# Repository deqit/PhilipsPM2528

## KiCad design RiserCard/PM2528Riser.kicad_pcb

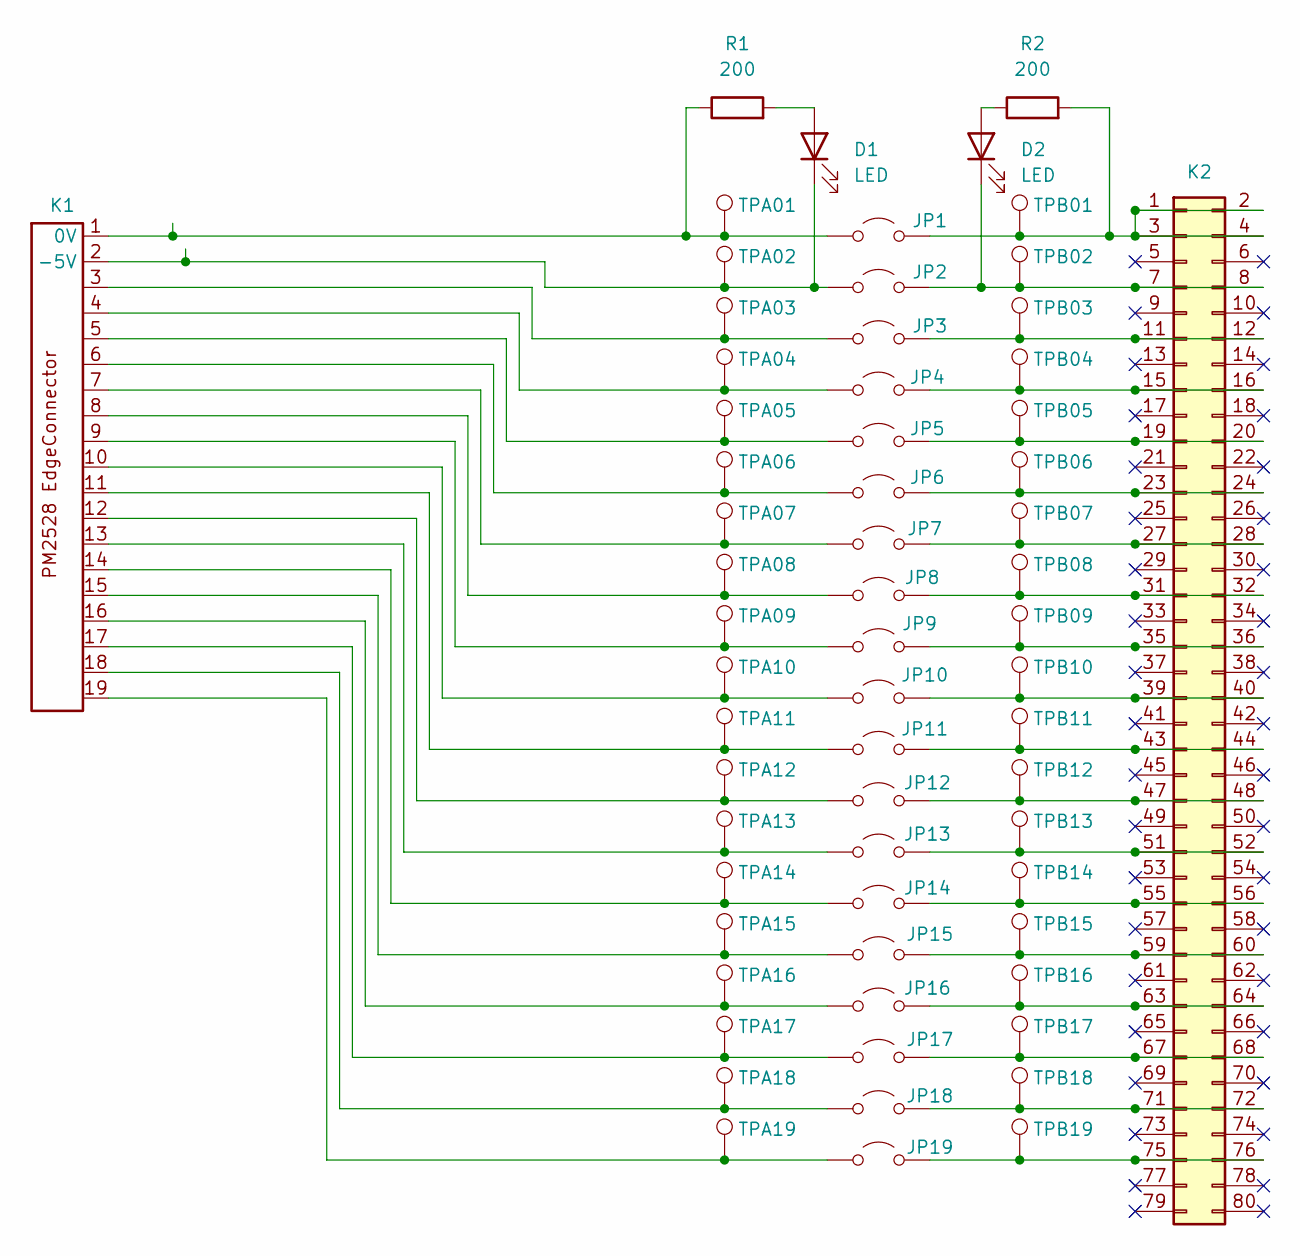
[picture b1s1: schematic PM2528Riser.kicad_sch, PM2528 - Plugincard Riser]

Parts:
D1, D2: LED; LED_0805_2012Metric
JP1, JP2, JP3, JP4, JP5, JP6, JP7, JP8, JP9, JP10, JP11, JP12, JP13, JP14, JP15, JP16, JP17, JP18, JP19: Jumper_2_Open; PinHeader_1x02_P2.54mm_Vertical
K1: PM2528_RiserCardConnector
K2: Conn_02x40_Odd_Even; CONN EDGE DUAL FMALE 80POS 0.100
R1, R2: 200; R_0805_2012Metric_Pad1.20x1.40mm_HandSolder
TPA01, TPA02, TPA03, TPA04, TPA05, TPA06, TPA07, TPA08, TPA09, TPA10, TPA11, TPA12, TPA13, TPA14, TPA15, TPA16, TPA17, TPA18, TPA19: TestPoint; Pin_D1.0mm_L10.0mm
TPB01, TPB02, TPB03, TPB04, TPB05, TPB06, TPB07, TPB08, TPB09, TPB10, TPB11, TPB12, TPB13, TPB14, TPB15, TPB16, TPB17, TPB18, TPB19: TestPoint; TestPoint_Loop_D1.80mm_Drill1.0mm_Beaded

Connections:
unnamed: D1.2 (A), R1.2
unnamed: D1.1 (K), JP2.1 (A), K1.2 (-5V), TPA02.1
unnamed: D2.2 (A), R2.1
unnamed: D2.1 (K), JP2.2 (B), K2.7, K2.8, TPB02.1
unnamed: JP1.1 (A), K1.1 (0V), R1.1, TPA01.1
unnamed: JP1.2 (B), K2.1, K2.2, K2.3, K2.4, R2.2, TPB01.1
unnamed: JP3.1 (A), K1.3, TPA03.1
unnamed: JP3.2 (B), K2.11, K2.12, TPB03.1
unnamed: JP4.1 (A), K1.4, TPA04.1
unnamed: JP4.2 (B), K2.15, K2.16, TPB04.1
unnamed: JP5.1 (A), K1.5, TPA05.1
unnamed: JP5.2 (B), K2.19, K2.20, TPB05.1
unnamed: JP6.1 (A), K1.6, TPA06.1
unnamed: JP6.2 (B), K2.23, K2.24, TPB06.1
unnamed: JP7.1 (A), K1.7, TPA07.1
unnamed: JP7.2 (B), K2.27, K2.28, TPB07.1
unnamed: JP8.1 (A), K1.8, TPA08.1
unnamed: JP8.2 (B), K2.31, K2.32, TPB08.1
unnamed: JP9.1 (A), K1.9, TPA09.1
unnamed: JP9.2 (B), K2.35, K2.36, TPB09.1
unnamed: JP10.1 (A), K1.10, TPA10.1
unnamed: JP10.2 (B), K2.39, K2.40, TPB10.1
unnamed: JP11.1 (A), K1.11, TPA11.1
unnamed: JP11.2 (B), K2.43, K2.44, TPB11.1
unnamed: JP12.1 (A), K1.12, TPA12.1
unnamed: JP12.2 (B), K2.47, K2.48, TPB12.1
unnamed: JP13.1 (A), K1.13, TPA13.1
unnamed: JP13.2 (B), K2.51, K2.52, TPB13.1
unnamed: JP14.1 (A), K1.14, TPA14.1
unnamed: JP14.2 (B), K2.55, K2.56, TPB14.1
unnamed: JP15.1 (A), K1.15, TPA15.1
unnamed: JP15.2 (B), K2.59, K2.60, TPB15.1
unnamed: JP16.1 (A), K1.16, TPA16.1
unnamed: JP16.2 (B), K2.63, K2.64, TPB16.1
unnamed: JP17.1 (A), K1.17, TPA17.1
unnamed: JP17.2 (B), K2.67, K2.68, TPB17.1
unnamed: JP18.1 (A), K1.18, TPA18.1
unnamed: JP18.2 (B), K2.71, K2.72, TPB18.1
unnamed: JP19.1 (A), K1.19, TPA19.1
unnamed: JP19.2 (B), K2.75, K2.76, TPB19.1

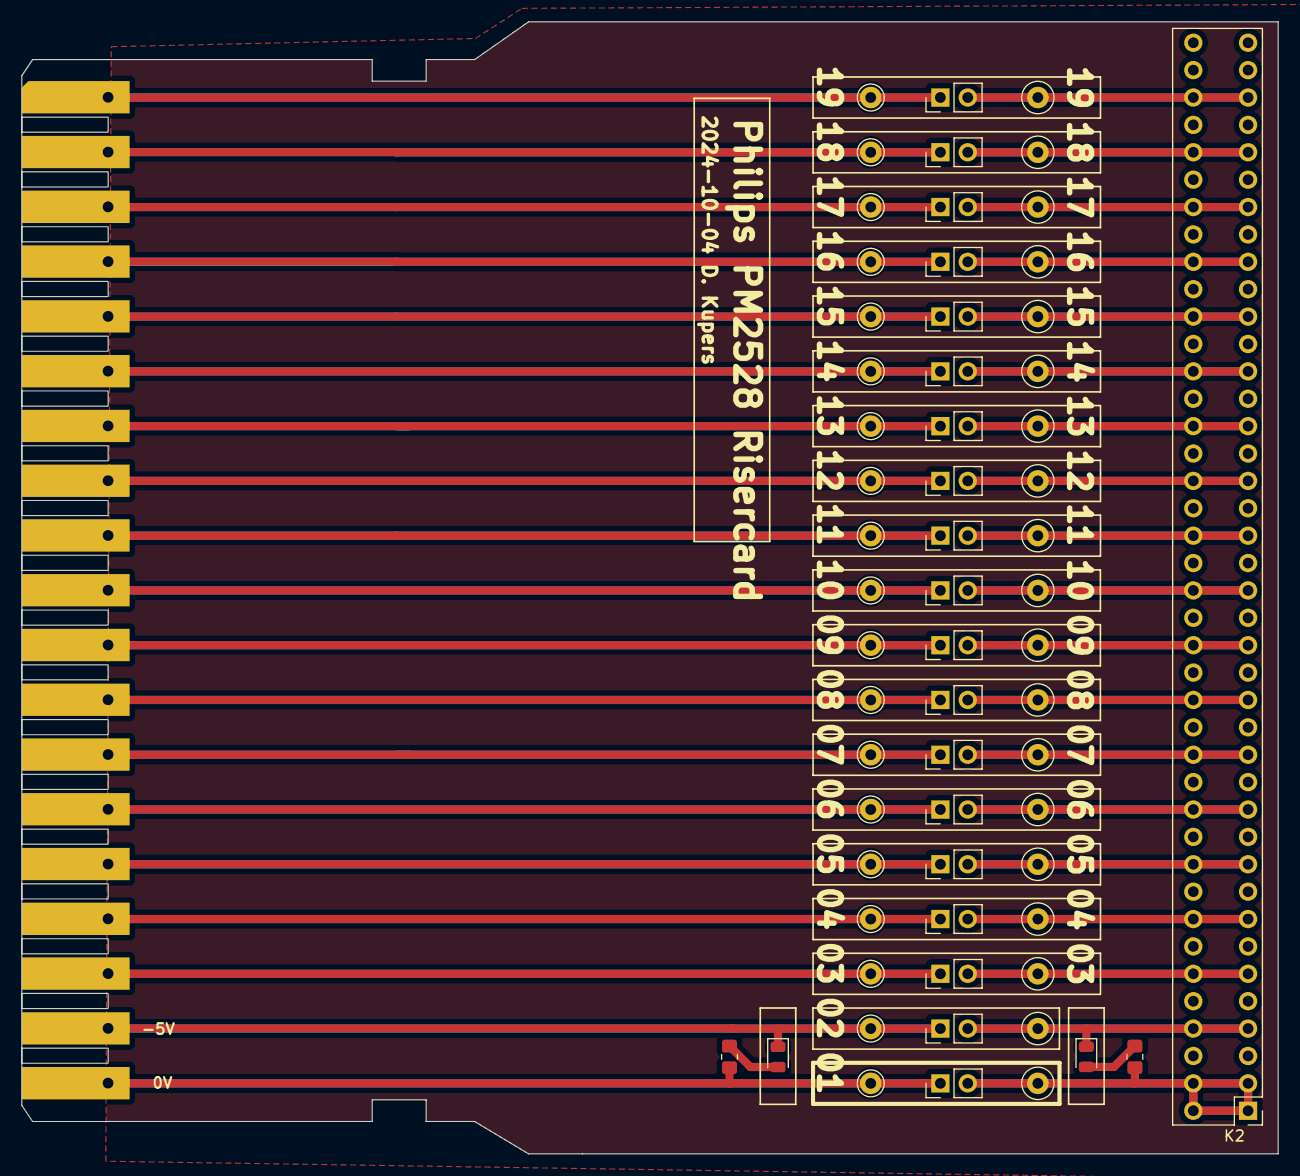
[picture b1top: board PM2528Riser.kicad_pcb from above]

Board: 2 copper layers, 116.5 x 105.0 mm, 63 parts (0 on the bottom side), 40 nets.

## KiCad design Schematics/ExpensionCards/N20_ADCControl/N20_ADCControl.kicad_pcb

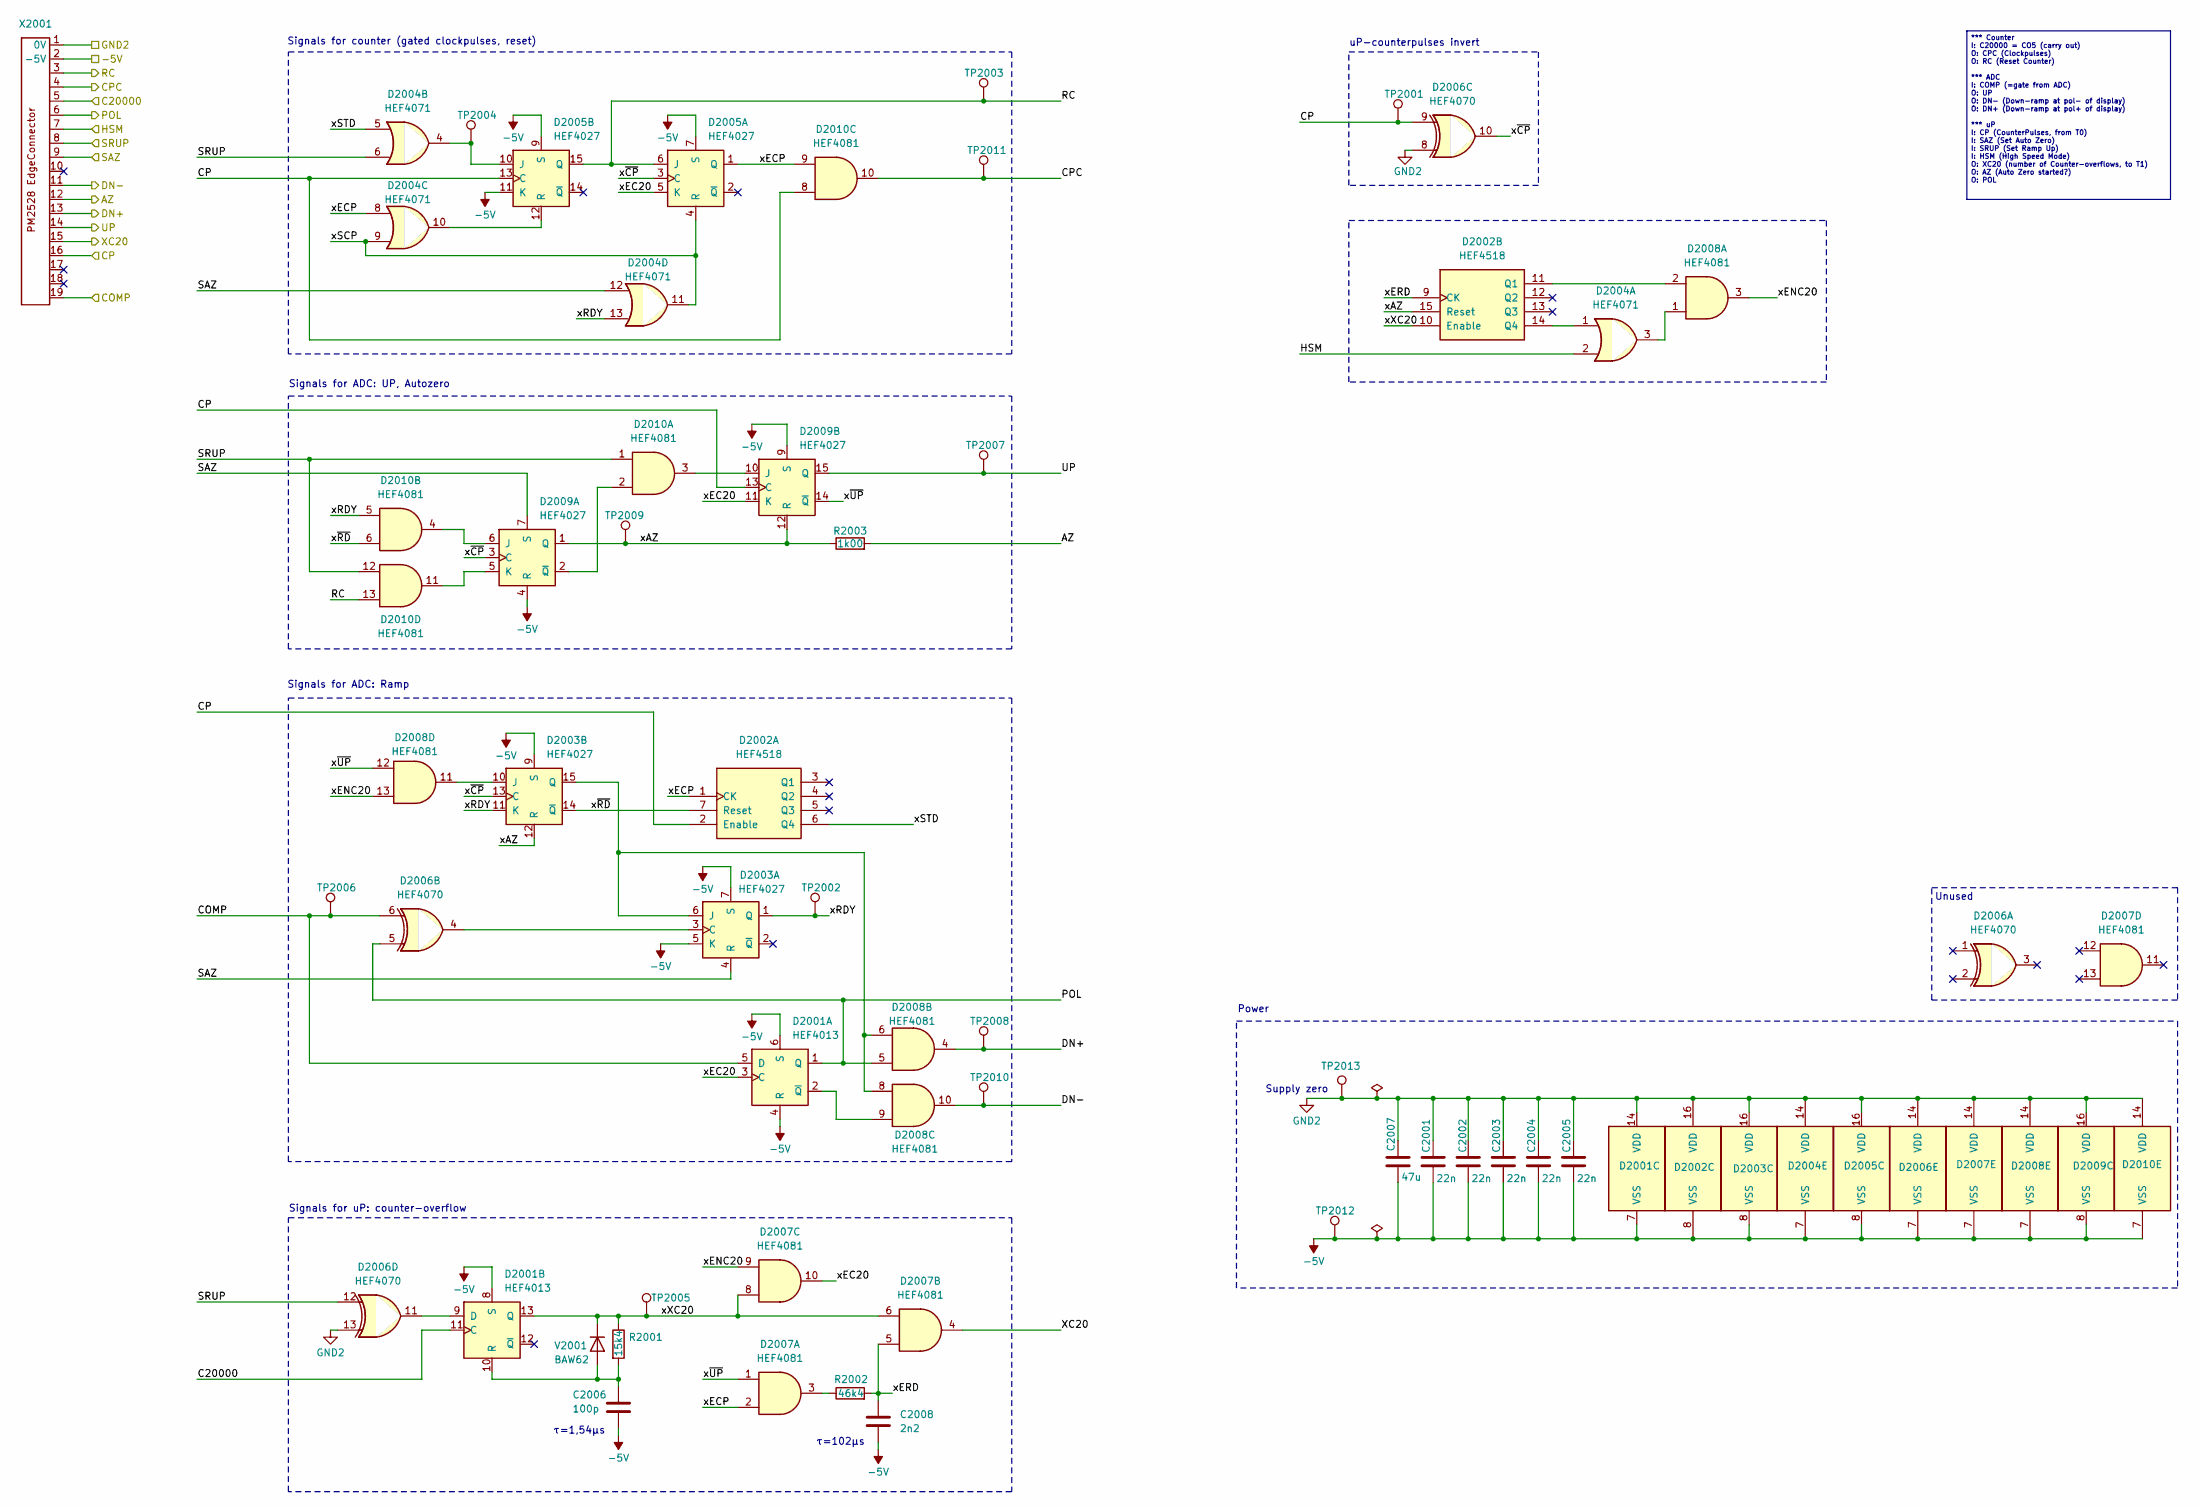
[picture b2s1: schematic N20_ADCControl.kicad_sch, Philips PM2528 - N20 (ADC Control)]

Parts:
C2001, C2002, C2003, C2004, C2005: 22n; C_Disc_D5.0mm_W2.5mm_P5.00mm
C2006: 100p; C_Disc_D5.0mm_W2.5mm_P5.00mm
C2007: 47u; CP_Axial_L10.0mm_D6.0mm_P15.00mm_Horizontal
C2008: 2n2; C_Disc_D5.0mm_W2.5mm_P5.00mm
D2001: HEF4013; DIP-14_W7.62mm
D2002: HEF4518; DIP-16_W7.62mm
D2003, D2005, D2009: HEF4027; DIP-16_W7.62mm
D2004: HEF4071; DIP-14_W7.62mm
D2006: HEF4070; DIP-14_W7.62mm
D2007, D2008, D2010: HEF4081; DIP-14_W7.62mm
R2001: 15k4; R_Axial_DIN0207_L6.3mm_D2.5mm_P10.16mm_Horizontal
R2002: 46k4; R_Axial_DIN0207_L6.3mm_D2.5mm_P10.16mm_Horizontal
R2003: 1k00; R_Axial_DIN0207_L6.3mm_D2.5mm_P10.16mm_Horizontal
TP2001, TP2002, TP2003, TP2004, TP2005, TP2006, TP2007, TP2008, TP2009, TP2010, TP2011, TP2012, TP2013: TestPoint; Pin_D0.9mm_L10.0mm_W2.4mm_FlatFork
V2001: BAW62; D_T-1_P10.16mm_Horizontal
X2001: PM2528_RiserCardConnector

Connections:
-5V: C2001.2, C2002.2, C2003.2, C2004.2, C2005.2, C2006.2, C2007.2, C2008.2, D2001.4 (R), D2001.6 (S), D2001.7 (VSS), D2001.8 (S), D2002.8 (VSS), D2003.5 (K), D2003.7 (S), D2003.8 (VSS), D2003.9 (S), D2004.7 (VSS), D2005.7 (S), D2005.8 (VSS), D2005.9 (S), D2005.11 (K), D2006.7 (VSS), D2007.7 (VSS), D2008.7 (VSS), D2009.4 (R), D2009.8 (VSS), D2009.9 (S), D2010.7 (VSS), TP2012.1, X2001.2 (-5V)
/AZ: R2003.2, X2001.12
/C20000: D2001.11 (C), X2001.5
/COMP: D2001.5 (D), D2006.6, TP2006.1, X2001.19
/CP: D2002.2 (Enable), D2005.13 (C), D2006.9, D2009.13 (C), D2010.8, TP2001.1, X2001.16
/CPC: D2010.10, TP2011.1, X2001.4
/DN+: D2008.4, TP2008.1, X2001.13
/DN-: D2008.10, TP2010.1, X2001.11
/HSM: D2004.2, X2001.7
/POL: D2001.1 (Q), D2006.5, D2008.5, X2001.6
/RC: D2005.6 (J), D2005.15 (Q), D2010.13, TP2003.1, X2001.3
/SAZ: D2003.4 (R), D2004.12, D2009.7 (S), X2001.9
/SRUP: D2004.6, D2006.12, D2010.1, D2010.12, X2001.8
/UP: D2009.15 (Q), TP2007.1, X2001.14
/XC20: D2007.4, X2001.15
/xAZ: D2002.15 (Reset), D2003.12 (R), D2009.1 (Q), D2009.12 (R), R2003.1, TP2009.1
/xEC20: D2001.3 (C), D2005.5 (K), D2007.10, D2009.11 (K)
/xECP: D2002.1 (CK), D2004.8, D2005.1 (Q), D2007.2, D2010.9
/xENC20: D2007.9, D2008.3, D2008.13
/xERD: C2008.1, D2002.9 (CK), D2007.5, R2002.2
/xRDY: D2003.1 (Q), D2003.11 (K), D2004.13, D2010.5, TP2002.1
/xSCP: D2004.9, D2004.11, D2005.4 (R)
/xSTD: D2002.6 (Q4), D2004.5
/xXC20: D2001.13 (Q), D2002.10 (Enable), D2007.6, D2007.8, R2001.1, TP2005.1, V2001.1 (K)
/x~CP: D2003.13 (C), D2005.3 (C), D2006.10, D2009.3 (C)
/x~RD: D2002.7 (Reset), D2003.14 (~Q), D2010.6
/x~UP: D2007.1, D2008.12, D2009.14 (~Q)
GND2: C2001.1, C2002.1, C2003.1, C2004.1, C2005.1, C2007.1, D2001.14 (VDD), D2002.16 (VDD), D2003.16 (VDD), D2004.14 (VDD), D2005.16 (VDD), D2006.8, D2006.13, D2006.14 (VDD), D2007.14 (VDD), D2008.14 (VDD), D2009.16 (VDD), D2010.14 (VDD), TP2013.1, X2001.1 (0V)
unnamed: D2001.2 (~Q), D2008.9
unnamed: D2001.9 (D), D2006.11
unnamed: C2006.1, D2001.10 (R), R2001.2, V2001.2 (A)
unnamed: D2002.11 (Q1), D2008.2
unnamed: D2002.14 (Q4), D2004.1
unnamed: D2003.3 (C), D2006.4
unnamed: D2003.6 (J), D2003.15 (Q), D2008.6, D2008.8
unnamed: D2003.10 (J), D2008.11
unnamed: D2004.3, D2008.1
unnamed: D2004.4, D2005.10 (J), TP2004.1
unnamed: D2004.10, D2005.12 (R)
unnamed: D2007.3, R2002.1
unnamed: D2009.6 (J), D2010.4
unnamed: D2009.5 (K), D2010.11
unnamed: D2009.2 (~Q), D2010.2
unnamed: D2009.10 (J), D2010.3

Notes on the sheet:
τ=102μs
Signals for ADC: UP, Autozero
Signals for ADC: Ramp
Power
Supply zero
uP-counterpulses invert
Signals for counter (gated clockpulses, reset)
τ=1,54μs
Signals for uP: counter-overflow
Unused
*** Counter I: C20000 = CO5 (carry out) O: CPC (Clockpulses) O: RC (Reset Counter) *** ADC I: COMP (=gate from ADC) O: UP O: DN- (Down-ramp at pol- of display) O: DN+ (Down-ramp at pol+ of display) *** uP I: CP (CounterPulses, from T0) I: SAZ (Set Auto Zero) I: SRUP (Set Ramp Up) I: HSM (High Speed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

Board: 2 copper layers, 36 parts (0 on the bottom side), 44 nets, no tracks yet.

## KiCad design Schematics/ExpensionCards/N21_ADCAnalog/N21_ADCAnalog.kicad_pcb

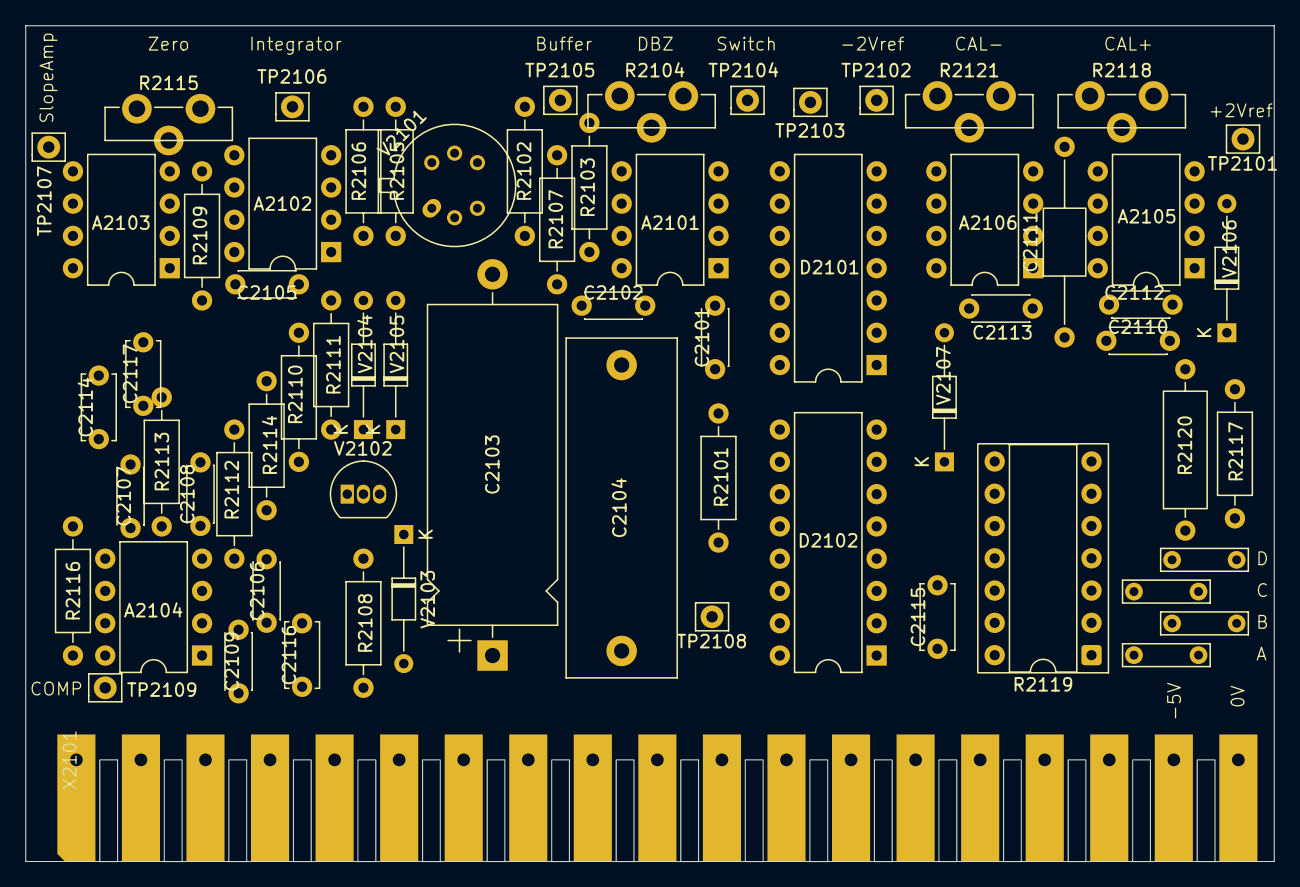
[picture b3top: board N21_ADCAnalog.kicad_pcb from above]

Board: 2 copper layers, 98.2 x 65.8 mm, 67 parts (0 on the bottom side), 54 nets, no tracks yet.

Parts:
A2101: LF356H; DIP-8_W7.62mm
A2102, A2105, A2106: LM201AN; DIP-8_W7.62mm
A2103: LF355H; DIP-8_W7.62mm
A2104: LM311N; DIP-8_W7.62mm
C2101: 10n/100V; C_Disc_D4.3mm_W1.9mm_P5.00mm
C2102, C2107, C2108, C2109: 22n/63V; C_Disc_D4.3mm_W1.9mm_P5.00mm
C2103: 162n/100V; CP_Axial_L25.0mm_D10.0mm_P30.00mm_Horizontal
C2104: 3u3/100V; C_Rect_L26.5mm_W8.5mm_P22.50mm_MKS4
C2105, C2112, C2113: 33p/100V; C_Disc_D4.3mm_W1.9mm_P5.00mm
C2106: 220p/500V; C_Disc_D4.3mm_W1.9mm_P5.00mm
C2110: 4n7/100V; C_Disc_D4.3mm_W1.9mm_P5.00mm
C2111: 4n22/63V; C_Axial_L5.1mm_D3.1mm_P15.00mm_Horizontal
C2114, C2117: 6u8/25V; C_Disc_D5.0mm_W2.5mm_P5.00mm
C2115, C2116: 22u/10V; C_Disc_D5.0mm_W2.5mm_P5.00mm
D2101: HEF4066; DIP-14_W7.62mm
D2102: HEF4104; DIP-16_W7.62mm
JP2101: A; TestPoint_Bridge_Pitch5.08mm_Drill0.7mm
JP2102: B; TestPoint_Bridge_Pitch5.08mm_Drill0.7mm
JP2103: C; TestPoint_Bridge_Pitch5.08mm_Drill0.7mm
JP2104: D; TestPoint_Bridge_Pitch5.08mm_Drill0.7mm
R2101: 8k66; R_Axial_DIN0207_L6.3mm_D2.5mm_P10.16mm_Horizontal
R2102: 140k; R_Axial_DIN0207_L6.3mm_D2.5mm_P10.16mm_Horizontal
R2103: 64k9; R_Axial_DIN0207_L6.3mm_D2.5mm_P10.16mm_Horizontal
R2104: 680k; Trimmer vertical
R2105, R2106: 21M1; R_Axial_DIN0207_L6.3mm_D2.5mm_P10.16mm_Horizontal
R2107: 24k9; R_Axial_DIN0207_L6.3mm_D2.5mm_P10.16mm_Horizontal
R2108: 40k2; R_Axial_DIN0207_L6.3mm_D2.5mm_P10.16mm_Horizontal
R2109: 5k9; R_Axial_DIN0207_L6.3mm_D2.5mm_P10.16mm_Horizontal
R2110: 121k; R_Axial_DIN0207_L6.3mm_D2.5mm_P10.16mm_Horizontal
R2111: 5k90; R_Axial_DIN0207_L6.3mm_D2.5mm_P10.16mm_Horizontal
R2112, R2113: 442; R_Axial_DIN0207_L6.3mm_D2.5mm_P10.16mm_Horizontal
R2114: 442k; R_Axial_DIN0207_L6.3mm_D2.5mm_P10.16mm_Horizontal
R2115: 47k; Trimmer vertical
R2116: 1k05; R_Axial_DIN0207_L6.3mm_D2.5mm_P10.16mm_Horizontal
R2117: 8k25; R_Axial_DIN0207_L6.3mm_D2.5mm_P10.16mm_Horizontal
R2118: 33; Trimmer vertical
R2119: OM528; DIP-14_W7.62mm_Socket
R2120: 590; R_Axial_DIN0309_L9.0mm_D3.2mm_P12.70mm_Horizontal
R2121: 100; Trimmer vertical
TP2101: +2Vref; Pin_D0.9mm_L10.0mm_W2.4mm_FlatFork
TP2102: -2Vref; Pin_D0.9mm_L10.0mm_W2.4mm_FlatFork
TP2103: 0Vref; Pin_D0.9mm_L10.0mm_W2.4mm_FlatFork
TP2104: Switch; Pin_D0.9mm_L10.0mm_W2.4mm_FlatFork
TP2105: Buffer; Pin_D0.9mm_L10.0mm_W2.4mm_FlatFork
TP2106: Integrator; Pin_D0.9mm_L10.0mm_W2.4mm_FlatFork
TP2107: Slope Amp; Pin_D0.9mm_L10.0mm_W2.4mm_FlatFork
TP2108: Input; Pin_D0.9mm_L10.0mm_W2.4mm_FlatFork
TP2109: Comp; Pin_D0.9mm_L10.0mm_W2.4mm_FlatFork
V2101: TO-78-6
V2102: BSV80; TO-92_Inline
V2103, V2104, V2105, V2106: BAW62; D_DO-34_SOD68_P10.16mm_Horizontal
V2107: BZV14; D_DO-34_SOD68_P10.16mm_Horizontal
X2101: PM2528_RiserCardConnector

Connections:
+5V: C2115.1, D2102.1 (Vddo), X2101.5
+15V: A2101.7 (V+), A2102.7 (V+), A2103.7 (V+), A2104.8 (V+), A2105.7 (V+), A2106.7 (V+), C2101.2, C2107.1, C2114.1, R2107.1, R2115.1, R2117.2, X2101.4
-5V: A2104.1 (GND), C2109.2, C2116.2, D2101.7 (VSS), D2102.8 (Vss), X2101.2 (-5V)
-15V: A2101.4 (V-), A2102.4 (V-), A2103.4 (V-), A2104.4 (V-), A2105.4 (V-), A2106.4 (V-), C2102.2, C2108.2, C2117.2, R2105.2, R2106.2, R2115.3, X2101.3
/+2VRef: C2110.2, D2101.11, R2117.1, R2118.2, R2118.3, R2119.8, TP2101.1, V2106.1 (K), X2101.7
/AZ: D2102.5, X2101.12
/COMP: A2104.7, R2116.2, TP2109.1, X2101.19
/DN+: D2102.12, X2101.13
/DN-: D2102.4, X2101.11
/INPUT: R2101.1, TP2108.1, X2101.9
/UP: D2102.11, X2101.14
/xAZ: D2101.5, D2102.6, V2103.1 (K)
/xDN+: D2101.12, D2102.13
/xDN-: D2101.6, D2102.3
/xUP: D2101.13, D2102.10
GND3: A2103.3 (+), C2104.2, C2110.1, C2111.2, D2101.4, D2102.15 (EN), D2102.16 (Vddi), R2113.2, R2119.10, TP2103.1, X2101.6, X2101.8, X2101.10
GND4: C2101.1, C2102.1, C2107.2, C2108.1, C2109.1, C2114.2, C2115.2, C2116.1, C2117.1, D2101.14 (VDD), R2108.2, R2116.1, V2104.1 (K), V2105.2 (A), X2101.1 (0V), X2101.18
unnamed: A2101.3 (+), D2101.2, D2101.3, D2101.9, D2101.10, TP2104.1
unnamed: A2101.2 (-), A2101.6, R2102.2, R2103.2, TP2105.1
unnamed: A2102.3 (+), R2106.1, V2101.4 (2S)
unnamed: A2102.2 (-), R2105.1, V2101.1 (1S)
unnamed: A2102.1 (BAL), C2105.1
unnamed: A2102.8 (C/B), C2105.2
unnamed: A2102.6, C2103.1, R2109.1, TP2106.1
unnamed: A2103.2 (-), R2109.2, R2110.1
unnamed: A2103.6, R2110.2, R2111.2, R2112.1, TP2107.1
unnamed: A2104.2 (+), C2106.2, R2104.1, R2104.2, R2113.1, R2114.1
unnamed: A2104.3 (-), C2106.1, R2112.2
unnamed: A2104.5 (BAL), A2104.6 (STRB)
unnamed: A2105.3 (+), R2119.6
unnamed: A2105.2 (-), A2106.2 (-), R2119.4
unnamed: A2105.1 (LOGIC_REFERENCE), C2112.2
unnamed: A2105.8 (~DISABLE), C2112.1
unnamed: A2106.3 (+), R2119.9
unnamed: A2106.1 (LOGIC_REFERENCE), C2113.2
unnamed: A2106.8 (~DISABLE), C2113.1
unnamed: C2111.1, D2101.8, R2119.12, TP2102.1
unnamed: D2101.1, R2101.2
unnamed: JP2101.1 (A), JP2102.1 (A), R2119.14
unnamed: R2119.1, R2120.1
unnamed: JP2103.1 (A), R2119.2
unnamed: JP2104.1 (A), R2119.11
unnamed: R2118.1, R2119.5
unnamed: R2103.1, R2104.3
unnamed: R2114.2, R2115.2
unnamed: R2120.2, R2121.3
unnamed: R2107.2, V2101.2 (1D), V2101.5 (2D)
unnamed: C2103.2, R2102.1, V2101.3 (1G)
unnamed: C2104.1, V2101.6 (2G), V2102.3 (S)
unnamed: R2111.1, V2102.1 (D), V2104.2 (A), V2105.1 (K)
unnamed: R2108.1, V2102.2 (G), V2103.2 (A)
unnamed: A2105.6, V2106.2 (A)
unnamed: A2106.6, R2121.1, R2121.2, V2107.2 (A)
unnamed: R2119.7, V2107.1 (K)

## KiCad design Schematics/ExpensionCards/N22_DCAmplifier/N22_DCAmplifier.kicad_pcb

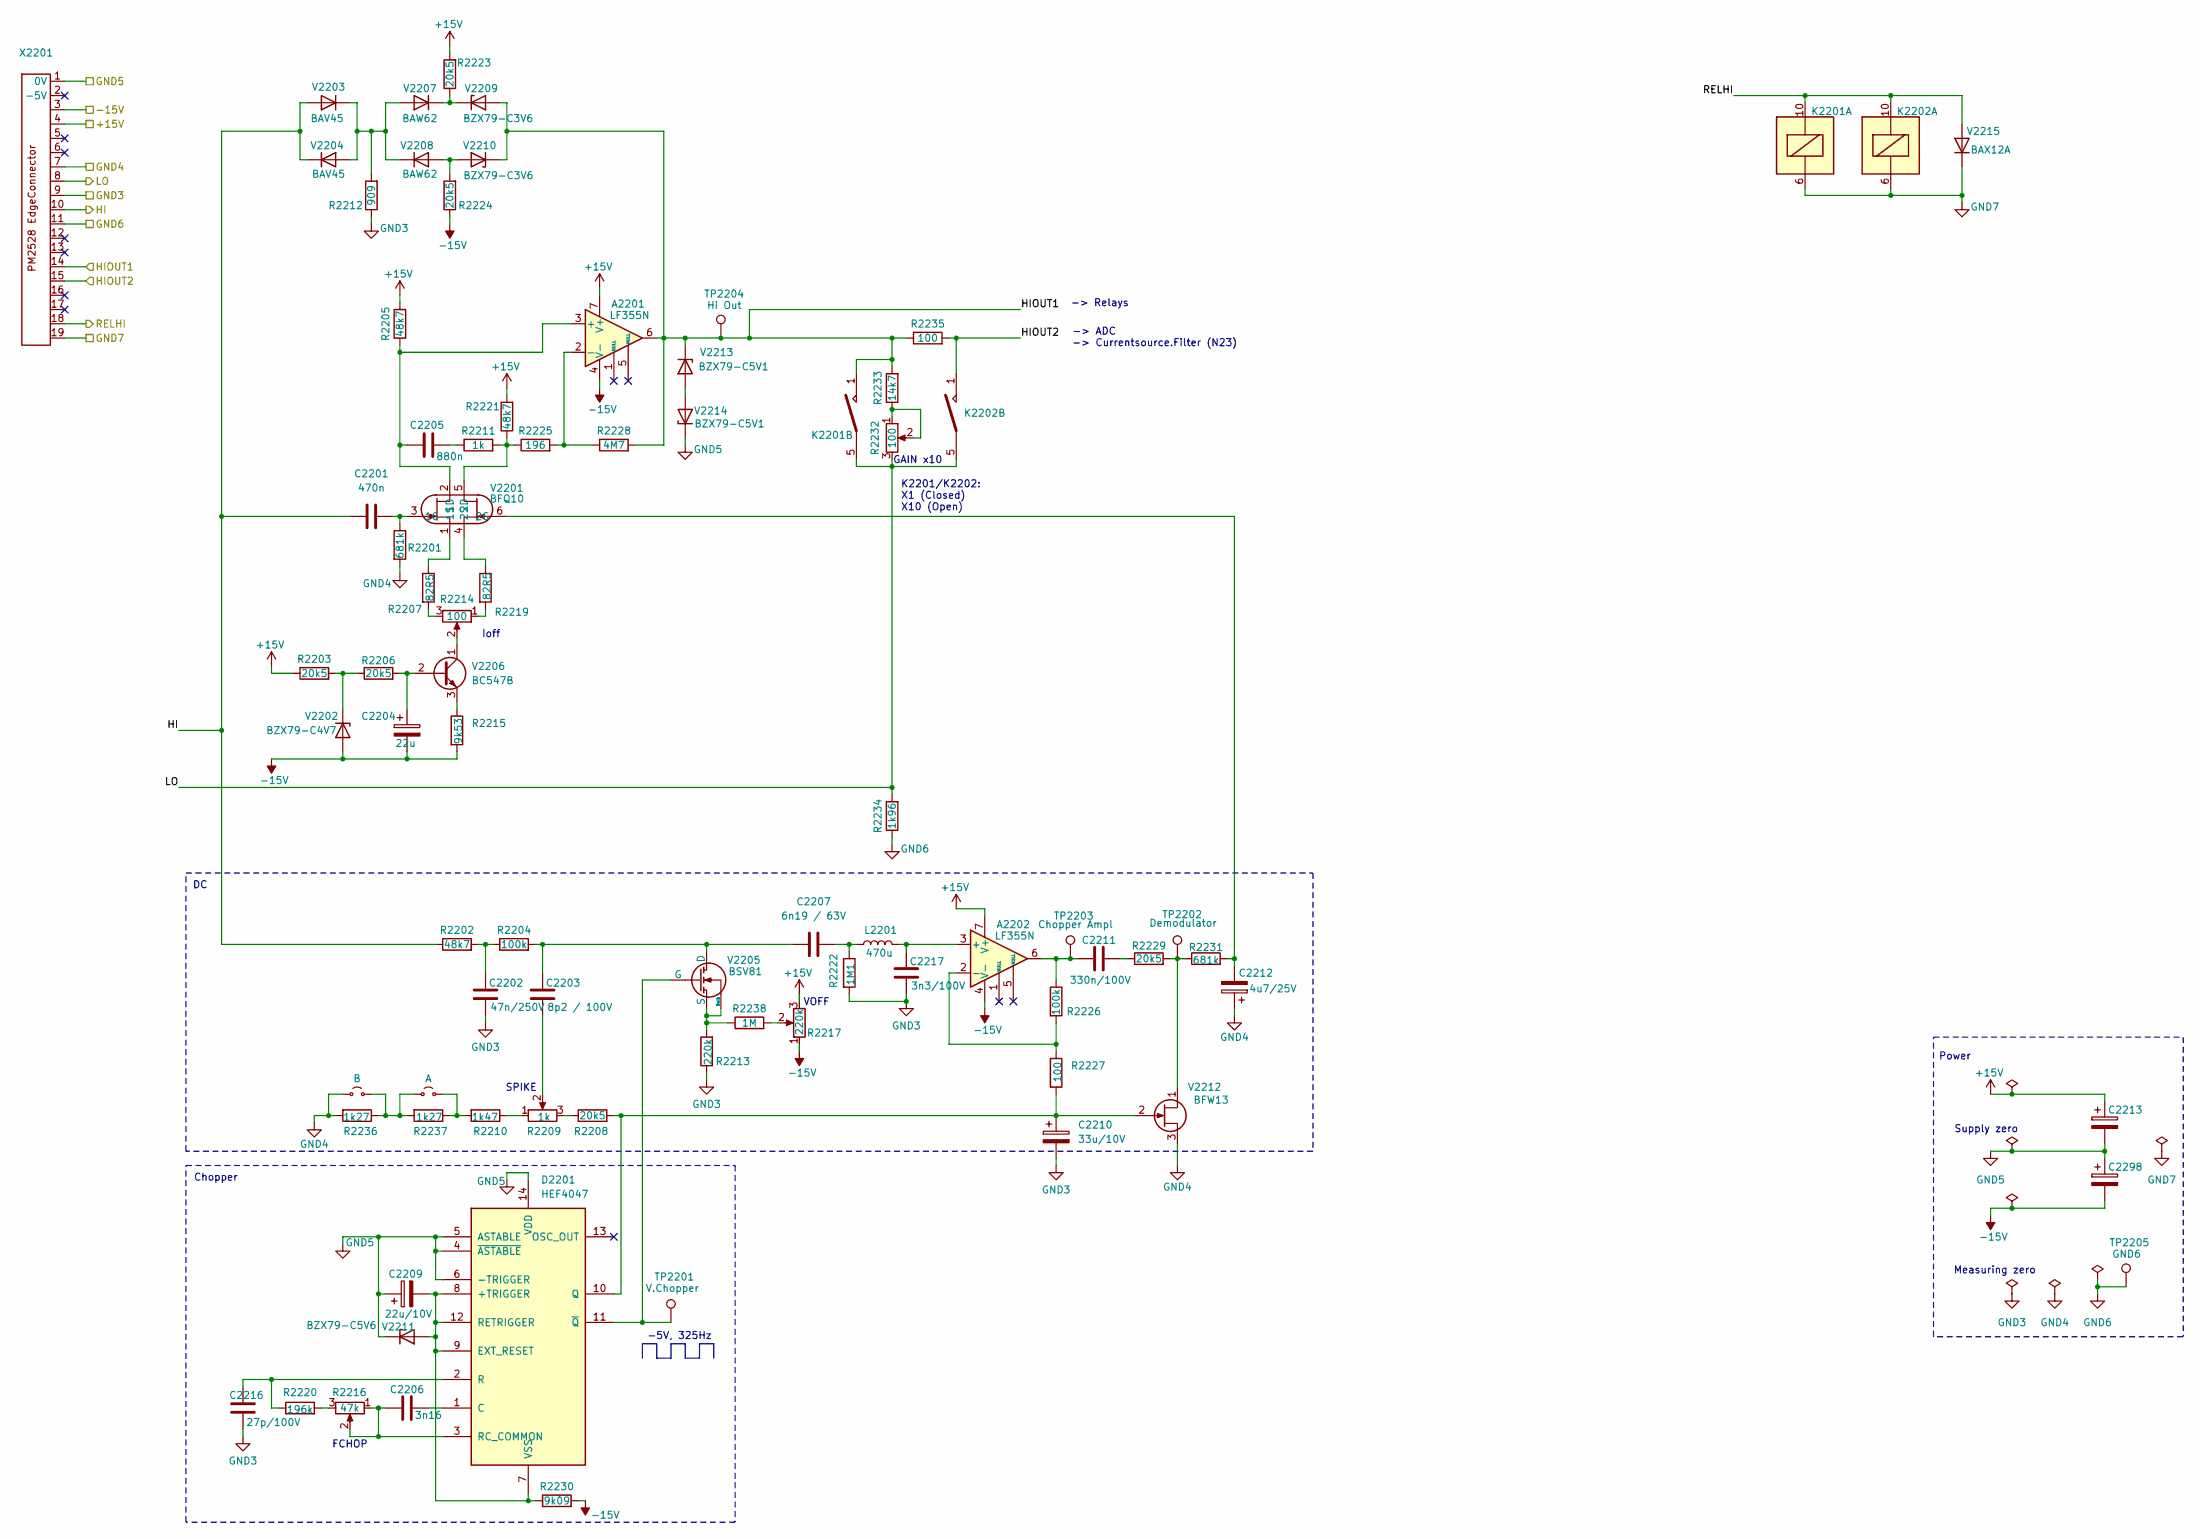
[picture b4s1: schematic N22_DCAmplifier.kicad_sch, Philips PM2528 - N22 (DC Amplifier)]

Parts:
A2201, A2202: LF355N; DIP-8_W7.62mm
C2201: 470n; C_Rect_L18.0mm_W6.0mm_P15.00mm_FKS3_FKP3
C2202: 47n/250V; C_Rect_L10.0mm_W4.0mm_P7.50mm_FKS3_FKP3
C2203: 8p2 / 100V; C_Disc_D4.3mm_W1.9mm_P5.00mm
C2204: 22u; CP_Radial_Tantal_D4.5mm_P5.00mm
C2205: 880n; C_Rect_L18.0mm_W5.0mm_P15.00mm_FKS3_FKP3
C2206: 3n16; C_Axial_L3.8mm_D2.6mm_P15.00mm_Horizontal
C2207: 6n19 / 63V; C_Axial_L3.8mm_D2.6mm_P15.00mm_Horizontal
C2209: 22u/10V; C_Disc_D5.0mm_W2.5mm_P5.00mm
C2210: 33u/10V; CP_Radial_Tantal_D4.5mm_P5.00mm
C2211: 330n/100V; C_Rect_L18.0mm_W5.0mm_P15.00mm_FKS3_FKP3
C2212: 4u7/25V; CP_Radial_Tantal_D4.5mm_P5.00mm
C2213, C2298: C_Polarized; C_Disc_D4.7mm_W2.5mm_P5.00mm
C2216: 27p/100V; C_Disc_D5.1mm_W3.2mm_P5.00mm
C2217: 3n3/100V; C_Disc_D4.3mm_W1.9mm_P5.00mm
D2201: HEF4047; DIP-14_W7.62mm
JP2201: A; TestPoint_Bridge_Pitch5.08mm_Drill0.7mm
JP2202: B; TestPoint_Bridge_Pitch5.08mm_Drill0.7mm
K2201, K2202: Reed relay assy
L2201: 470u; L_Axial_L9.5mm_D4.0mm_P15.24mm_Horizontal_Fastron_SMCC
R2201, R2231: 681k; R_Axial_DIN0207_L6.3mm_D2.5mm_P10.16mm_Horizontal
R2202, R2205, R2221: 48k7; R_Axial_DIN0207_L6.3mm_D2.5mm_P10.16mm_Horizontal
R2203, R2206, R2208, R2223, R2224, R2229: 20k5; R_Axial_DIN0207_L6.3mm_D2.5mm_P10.16mm_Horizontal
R2204, R2226: 100k; R_Axial_DIN0207_L6.3mm_D2.5mm_P10.16mm_Horizontal
R2207, R2219: 82R5; R_Axial_DIN0207_L6.3mm_D2.5mm_P10.16mm_Horizontal
R2209: 1k; Trimmer vertical
R2210: 1k47; R_Axial_DIN0207_L6.3mm_D2.5mm_P10.16mm_Horizontal
R2211: 1k; R_Axial_DIN0207_L6.3mm_D2.5mm_P10.16mm_Horizontal
R2212: 909; R_Axial_DIN0207_L6.3mm_D2.5mm_P10.16mm_Horizontal
R2213: 220k; R_Axial_DIN0207_L6.3mm_D2.5mm_P10.16mm_Horizontal
R2214, R2232: 100; Trimmer vertical
R2215: 9k53; R_Axial_DIN0207_L6.3mm_D2.5mm_P10.16mm_Horizontal
R2216: 47k; Trimmer vertical
R2217: 220k; Trimmer vertical
R2220: 196k; R_Axial_DIN0207_L6.3mm_D2.5mm_P10.16mm_Horizontal
R2222: 1M1; R_Axial_DIN0207_L6.3mm_D2.5mm_P10.16mm_Horizontal
R2225: 196; R_Axial_DIN0207_L6.3mm_D2.5mm_P10.16mm_Horizontal
R2227, R2235: 100; R_Axial_DIN0207_L6.3mm_D2.5mm_P10.16mm_Horizontal
R2228: 4M7; R_Axial_DIN0207_L6.3mm_D2.5mm_P10.16mm_Horizontal
R2230: 9k09; R_Axial_DIN0207_L6.3mm_D2.5mm_P10.16mm_Horizontal
R2233: 14k7; R_Axial_DIN0207_L6.3mm_D2.5mm_P10.16mm_Horizontal
R2234: 1k96; R_Axial_DIN0207_L6.3mm_D2.5mm_P10.16mm_Horizontal
R2236, R2237: 1k27; R_Axial_DIN0207_L6.3mm_D2.5mm_P10.16mm_Horizontal
R2238: 1M; R_Axial_DIN0309_L9.0mm_D3.2mm_P12.70mm_Horizontal
TP2201: V.Chopper; Pin_D0.9mm_L10.0mm_W2.4mm_FlatFork
TP2202: Demodulator; Pin_D0.9mm_L10.0mm_W2.4mm_FlatFork
TP2203: Chopper Ampl; Pin_D0.9mm_L10.0mm_W2.4mm_FlatFork
TP2204: Hi Out; Pin_D0.9mm_L10.0mm_W2.4mm_FlatFork
TP2205: GND6; Pin_D0.9mm_L10.0mm_W2.4mm_FlatFork
V2201: BFQ10; TO-75-6
V2202: BZX79-C4V7; D_DO-35_SOD27_P10.16mm_Horizontal
V2203, V2204: BAV45; D_DO-35_SOD27_P5.08mm_Vertical_AnodeUp
V2205: BSV81; TO-72-4
V2206: BC547B; TO-92_Inline
V2207, V2208: BAW62; D_DO-35_SOD27_P10.16mm_Horizontal
V2209, V2210: BZX79-C3V6; D_DO-35_SOD27_P10.16mm_Horizontal
V2211: BZX79-C5V6; D_DO-35_SOD27_P10.16mm_Horizontal
V2212: BFW13; TO-72-4
V2213, V2214: BZX79-C5V1; D_DO-35_SOD27_P12.70mm_Horizontal
V2215: BAX12A; D_DO-35_SOD27_P10.16mm_Horizontal
X2201: PM2528_RiserCardConnector

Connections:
+15V: A2201.7 (V+), A2202.7 (V+), C2213.1, R2203.1, R2205.2, R2217.3, R2221.2, R2223.2, X2201.4
-15V: A2201.4 (V-), A2202.4 (V-), C2204.2, C2298.2, R2215.2, R2217.1, R2224.1, R2230.2, V2202.2 (A), X2201.3
/HI: C2201.1, R2202.1, V2203.2 (A), V2204.1 (K), X2201.10
/HIOUT1: A2201.6, K2201.1, R2228.2, R2233.2, R2235.1, TP2204.1, V2209.2 (A), V2210.1 (K), V2213.1 (K), X2201.14
/HIOUT2: K2202.1, R2235.2, X2201.15
/LO: K2201.5, K2202.5, R2232.3, R2234.2, X2201.8
/RELHI: K2201.10, K2202.10, V2215.2 (A), X2201.18
GND3: C2202.1, C2210.2, C2216.1, C2217.1, R2212.1, R2213.1, R2222.2, X2201.9
GND4: C2212.1, JP2202.1 (A), R2201.2, R2236.2, V2212.3 (S), X2201.7
GND5: C2209.1, C2213.2, C2298.1, D2201.4 (~ASTABLE), D2201.5 (ASTABLE), D2201.6 (-TRIGGER), D2201.14 (VDD), V2211.1 (K), V2214.1 (K), X2201.1 (0V)
GND6: R2234.1, TP2205.1, X2201.11
GND7: K2201.6, K2202.6, V2215.1 (K), X2201.19
unnamed: A2201.3 (+), C2205.1, R2205.1, V2201.2 (1D)
unnamed: A2201.2 (-), R2225.2, R2228.1
unnamed: A2202.3 (+), C2217.2, L2201.2
unnamed: A2202.2 (-), R2226.2, R2227.1
unnamed: A2202.6, C2211.1, R2226.1, TP2203.1
unnamed: C2202.2, R2202.2, R2204.1
unnamed: C2203.1, R2209.2
unnamed: C2205.2, R2211.1
unnamed: C2207.2, L2201.1, R2222.1
unnamed: C2211.2, R2229.1
unnamed: C2209.2, D2201.7 (VSS), D2201.8 (+TRIGGER), D2201.9 (EXT_RESET), D2201.12 (RETRIGGER), R2230.1, V2211.2 (A)
unnamed: C2206.2, D2201.1 (C)
unnamed: C2210.1, D2201.10 (Q), R2208.2, R2227.2, V2212.2 (G)
unnamed: C2216.2, D2201.2 (R), R2220.1
unnamed: C2206.1, D2201.3 (RC_COMMON), R2216.1, R2216.2
unnamed: D2201.11 (~Q), TP2201.1, V2205.2 (G)
unnamed: JP2201.1 (A), JP2202.2 (B), R2236.1, R2237.2
unnamed: JP2201.2 (B), R2210.2, R2237.1
unnamed: R2207.2, R2214.3
unnamed: R2208.1, R2209.3
unnamed: R2209.1, R2210.1
unnamed: R2214.1, R2219.2
unnamed: R2216.3, R2220.2
unnamed: R2217.2, R2238.2
unnamed: R2232.1, R2232.2, R2233.1
unnamed: C2201.2, R2201.1, V2201.3 (1G)
unnamed: R2207.1, V2201.1 (1S)
unnamed: R2211.2, R2221.1, R2225.1, V2201.5 (2D)
unnamed: C2212.2, R2231.2, V2201.6 (2G)
unnamed: R2219.1, V2201.4 (2S)
unnamed: R2203.2, R2206.1, V2202.1 (K)
unnamed: R2212.2, V2203.1 (K), V2204.2 (A), V2207.2 (A), V2208.1 (K)
unnamed: R2213.2, R2238.1, V2205.3 (S), V2205.4 (Bulk)
unnamed: C2203.2, C2207.1, R2204.2, V2205.1 (D)
unnamed: C2204.1, R2206.2, V2206.2 (B)
unnamed: R2214.2, V2206.1 (C)
unnamed: R2215.1, V2206.3 (E)
unnamed: R2223.1, V2207.1 (K), V2209.1 (K)
unnamed: R2224.2, V2208.2 (A), V2210.2 (A)
unnamed: R2229.2, R2231.1, TP2202.1, V2212.1 (D)
unnamed: V2213.2 (A), V2214.2 (A)

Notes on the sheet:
-> Relays
-> ADC -> Currentsource.Filter (N23)
FCHOP
SPIKE
Supply zero
GAIN x10
K2201/K2202: X1 (Closed) X10 (Open)
VOFF
Chopper
-5V, 325Hz
Power
Measuring zero
Ioff

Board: 2 copper layers, 81 parts (0 on the bottom side), 53 nets, no tracks yet.
